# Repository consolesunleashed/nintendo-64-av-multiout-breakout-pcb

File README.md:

# Nintendo 64 AV Multiout Breakout PCB

A simple little PCB to help when RGB modding an N64. Add this little PCB to the multiout’s PCB pins and solder wires to this PCB instead of directly to the pins. Much neater. There's a jumper to rout the sync to different output pins.

## Version History

- v1 - 30/07/2021

## License

If you use this in any way, shape or form, you must include a link back to this repository and mention me by name on any sales pages and social media posts. Not only will this help me to keep designing mod kits and offering them to the community, but it is basic common courtesy as well. Don't be a douchebag. :)

Also this 'GNU GENERAL PUBLIC LICENSE Version 2, June 1991'.

## Donate

Working on designs to release for free can be both time consuming and expensive. If you like what I do, a small donation will go a long way in helping me continue to serve the modding community as best as I can, with many more free and original guides, designs, and ideas to come.

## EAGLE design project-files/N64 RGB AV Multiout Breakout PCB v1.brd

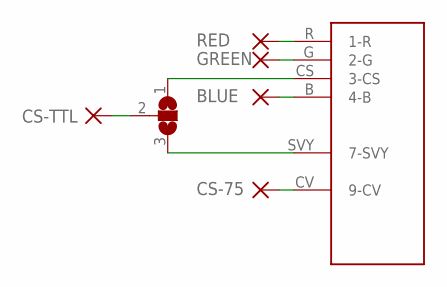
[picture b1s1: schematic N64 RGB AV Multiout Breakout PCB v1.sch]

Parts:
BLUE: BLUE; RECTANGLE-1,27X2,54
CS-75: CS-75; RECTANGLE-1,27X2,54
CS-TTL: CS-TTL; RECTANGLE-1,27X2,54
GREEN: GREEN; RECTANGLE-1,27X2,54
N64-MULTIOUT: N64-MULTIOUT
RED: RED; RECTANGLE-1,27X2,54
SJ1: JUMPER-3JUMPER-3; JUMPER-3

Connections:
unnamed: N64-MULTIOUT.R (1-R), RED.1
unnamed: GREEN.1, N64-MULTIOUT.G (2-G)
unnamed: BLUE.1, N64-MULTIOUT.B (4-B)
unnamed: CS-TTL.1, SJ1.2
unnamed: N64-MULTIOUT.CS (3-CS), SJ1.1
unnamed: N64-MULTIOUT.SVY (7-SVY), SJ1.3
unnamed: CS-75.1, N64-MULTIOUT.CV (9-CV)

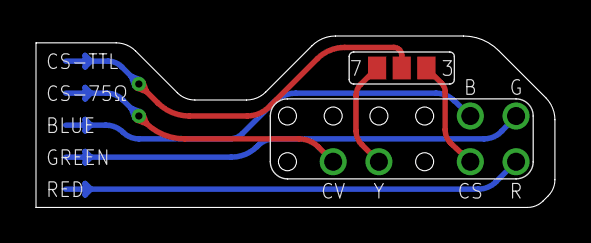
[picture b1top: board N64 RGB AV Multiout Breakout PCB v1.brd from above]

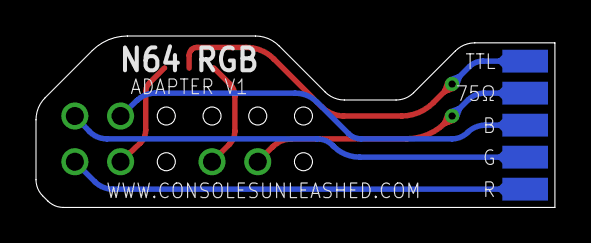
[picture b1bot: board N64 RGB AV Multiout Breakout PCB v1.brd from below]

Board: 2 copper layers, 28.8 x 9.5 mm, 7 parts (5 on the bottom side), 7 nets.
